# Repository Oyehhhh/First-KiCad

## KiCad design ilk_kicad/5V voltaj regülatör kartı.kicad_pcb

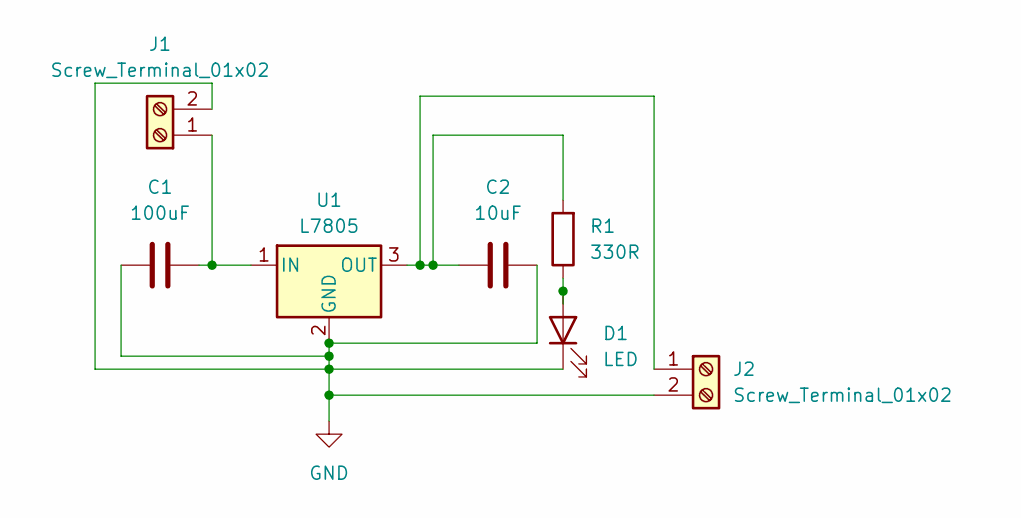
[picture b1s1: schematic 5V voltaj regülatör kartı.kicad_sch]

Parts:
C1: 100uF; CP_Radial_D5.0mm_P2.50mm
C2: 10uF; CP_Radial_D5.0mm_P2.50mm
D1: LED; LED_D5.0mm
J1, J2: Screw_Terminal_01x02; TerminalBlock_Phoenix_MKDS-1,5-2_1x02_P5.00mm_Horizontal
R1: 330R; R_Axial_DIN0207_L6.3mm_D2.5mm_P10.16mm_Horizontal
U1: L7805; TO-220-3_Vertical

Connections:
GND: C1.1, C2.2, D1.1 (K), J1.2, J2.2, U1.2 (GND)
unnamed: D1.2 (A), R1.1
unnamed: C1.2, J1.1, U1.1 (IN)
unnamed: C2.1, J2.1, R1.2, U1.3 (OUT)

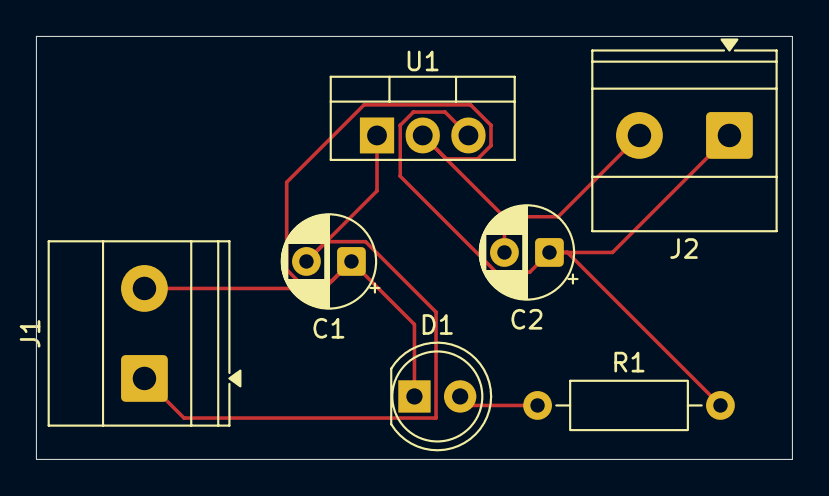
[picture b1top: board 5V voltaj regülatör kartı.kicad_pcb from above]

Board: 2 copper layers, 42.0 x 23.5 mm, 7 parts (0 on the bottom side), 4 nets.

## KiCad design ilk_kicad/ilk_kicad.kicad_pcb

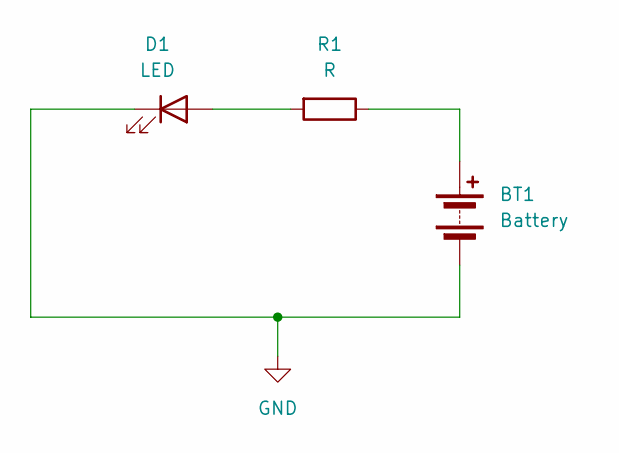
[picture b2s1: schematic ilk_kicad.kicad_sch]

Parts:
BT1: Battery; PinHeader_1x02_P2.54mm_Vertical
D1: LED; LED_D5.0mm
R1: R; R_Axial_DIN0207_L6.3mm_D2.5mm_P7.62mm_Horizontal

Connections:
GND: BT1.2 (-), D1.1 (K)
unnamed: BT1.1 (+), R1.1
unnamed: D1.2 (A), R1.2

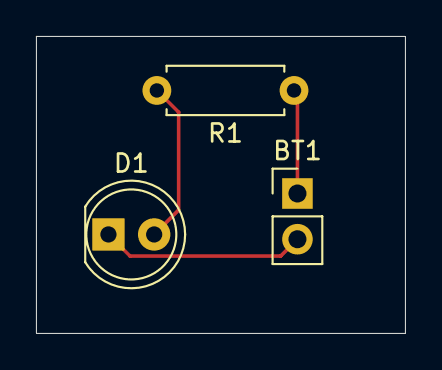
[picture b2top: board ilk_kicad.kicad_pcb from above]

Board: 2 copper layers, 20.5 x 16.5 mm, 3 parts (0 on the bottom side), 3 nets.
